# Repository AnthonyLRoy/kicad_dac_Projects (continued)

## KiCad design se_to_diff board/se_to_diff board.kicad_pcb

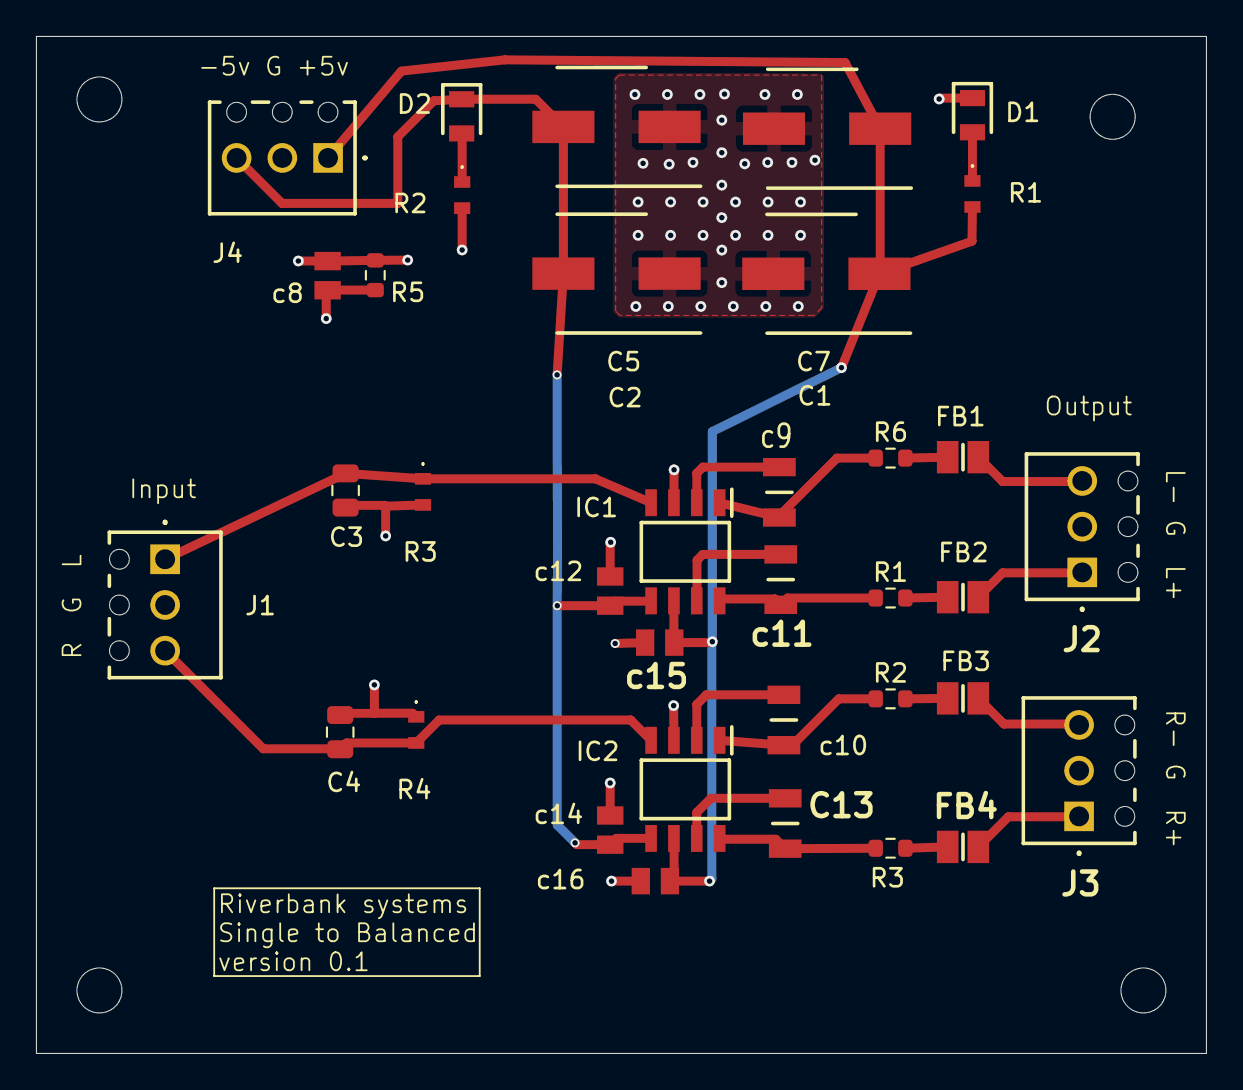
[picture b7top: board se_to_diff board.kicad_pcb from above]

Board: 4 copper layers, 65.0 x 56.5 mm, 40 parts (0 on the bottom side), 24 nets.

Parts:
C1, C2, C5, C7: 47u; CAPAE660X800N
C3, C4: 220p; C_0805_2012Metric
C13: 10u; CAPC3216X229N
D1, D2: LS_R976; LEDC2012X40N
FB1, FB2, FB3, FB4: NFZ2MSD101SZ10L; BEADC2016X120N
H1, H2, H3, H4: MountingHole; MountingHole_2.5mm
IC1, IC2: 1646S08-U; SOIC127P602X173-8N
J1, J2, J3, J4: 1725669
R1, R2#2, R3: 22; R_0603_1608Metric
R1#2, R2: 3k; ERJH3
R3#2, R4: 47k; ERJH3
R5: 10R; R_0603_1608Metric
R6: 22R; R_0603_1608Metric
c8, c12, c14, c15, c16: 100n; CAPC2012X94N
c9, c10, c11: 10u; CAPC3216X229N

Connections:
/Sout L +: FB2.1, R1.2
/Sout L -: FB1.1, R6.2
/Sout R +: FB4.1, R3.2
/Sout R -: FB3.1, R2#2.2
/in L: C3.2, IC1.4 (IN), J1.1, R3#2.1
/in R: C4.1, IC2.4 (IN), J1.3, R4.2
/out L +: IC1.8 (OUT+), R1.1, c11.2
/out L -: IC1.1 (OUT-), R6.1, c9.2
/out R +: C13.2, IC2.8 (OUT+), R3.1
/out R -: IC2.1 (OUT-), R2#2.1, c10.2
GND: C3.1, C4.2, IC1.3 (GND), IC2.3 (GND), J1.2, J2.2, J3.2, R3#2.2, R4.1, R5.2, c8.1
GND2: C1.2, C2.1, C5.1, C7.2, D1.1 (K), J4.2, R2.2, R5.1, c8.2, c12.1, c14.1, c15.1, c16.1
unnamed: D1.2 (A), R1#2.1
unnamed: D2.2 (A), R2.1
unnamed: FB1.2, J2.3
unnamed: FB2.2, J2.1
unnamed: FB3.2, J3.3
unnamed: FB4.2, J3.1
unnamed: IC1.7 (SNS+), c11.1
unnamed: IC1.2 (SNS-), c9.1
unnamed: C13.1, IC2.7 (SNS+)
unnamed: IC2.2 (SNS-), c10.1
VCC: C1.1, C7.1, IC1.6 (VCC), IC2.6 (VCC), J4.1, R1#2.2, c15.2, c16.2
VEE: C2.2, C5.2, D2.1 (K), IC1.5 (VEE), IC2.5 (VEE), J4.3, c12.2, c14.2

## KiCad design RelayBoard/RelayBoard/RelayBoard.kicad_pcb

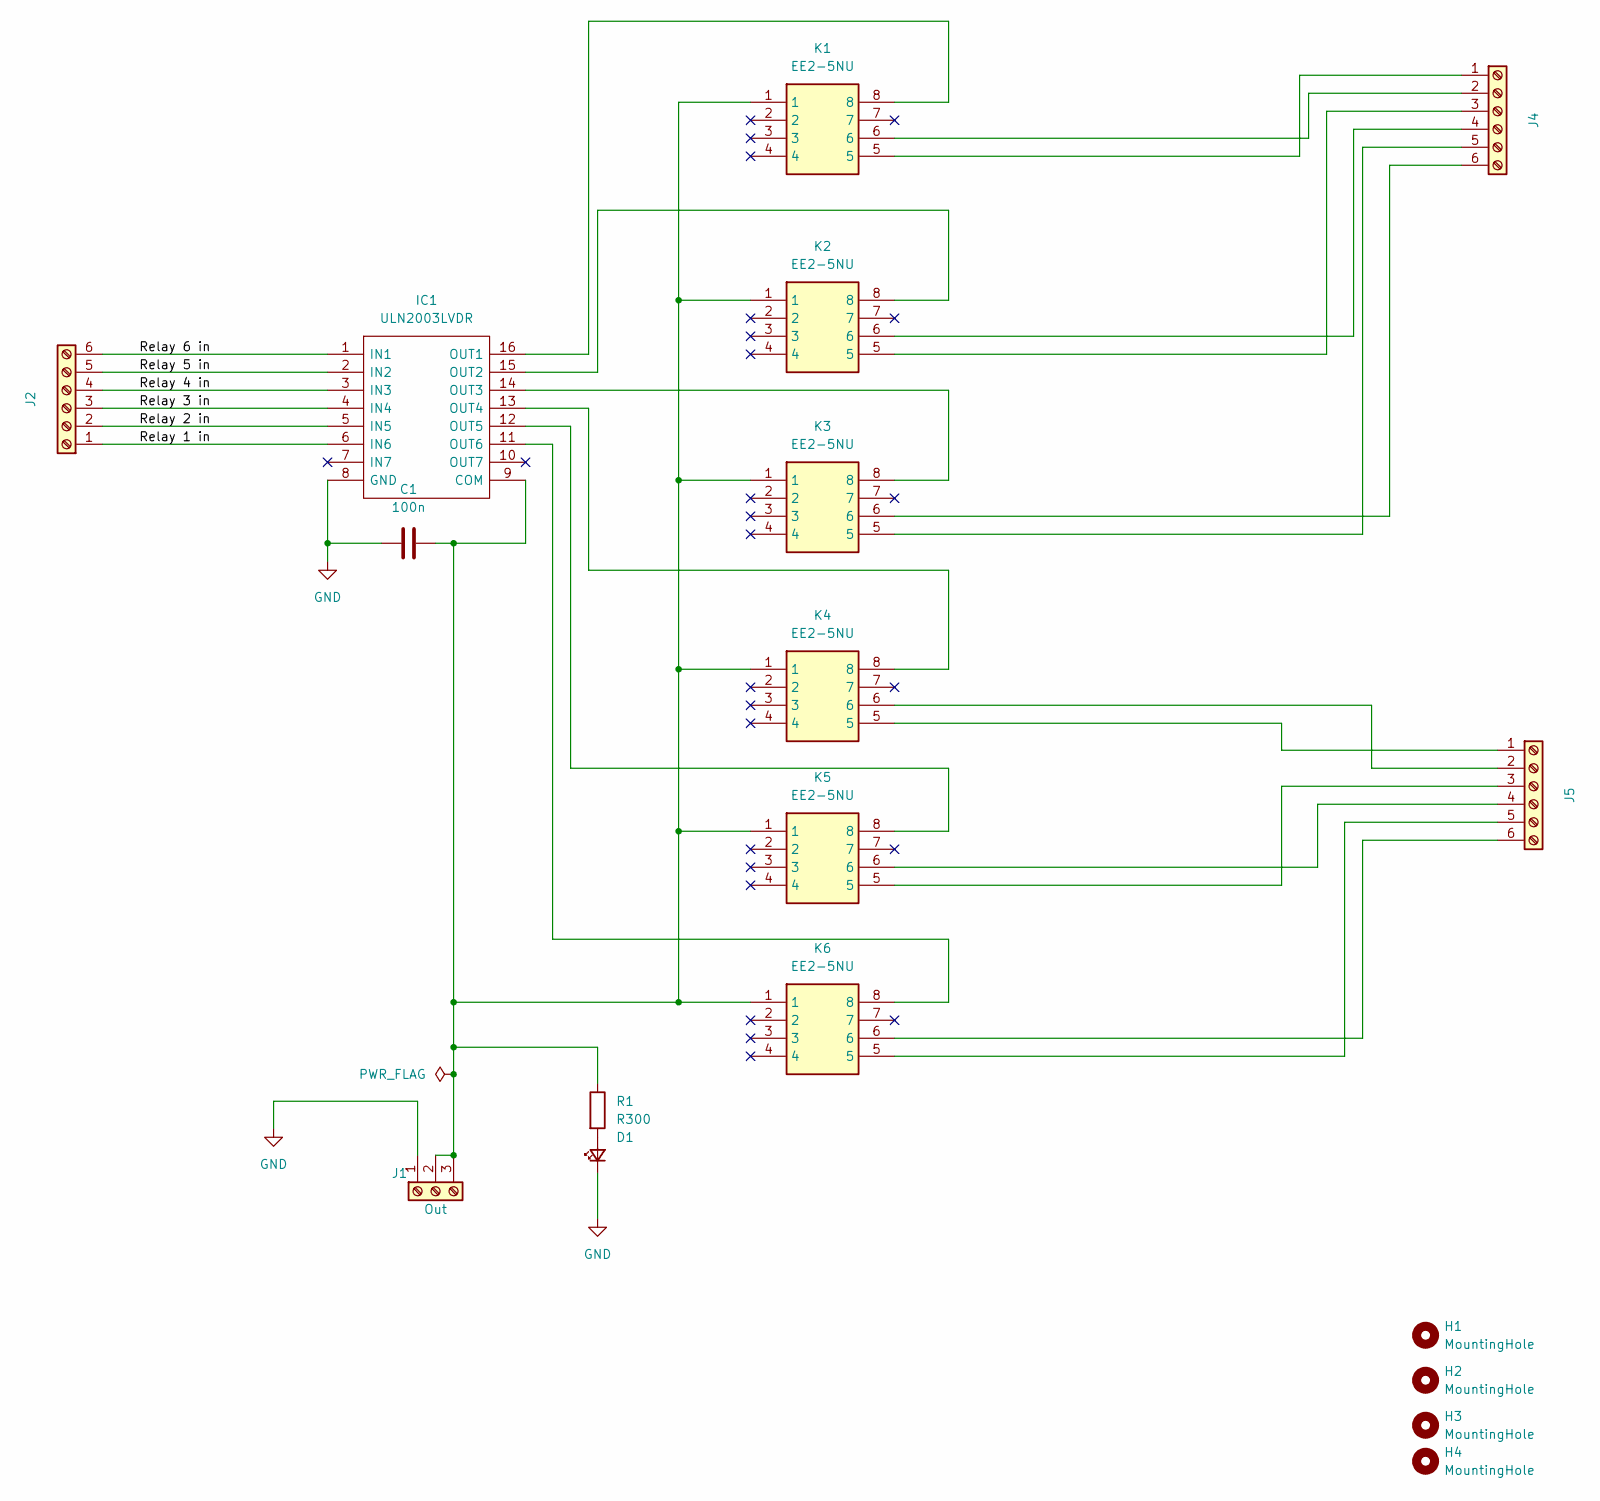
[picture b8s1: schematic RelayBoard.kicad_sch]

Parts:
C1: 100n; C_0805_2012Metric_Pad1.18x1.45mm_HandSolder
D1: LS_R976; LEDC2012X40N; Mouser Part Number 720-LSR976D5178
H1, H2, H3, H4: MountingHole; MountingHole_2.7mm_M2.5
IC1: ULN2003LVDR; SOIC127P780X200-16N; Manufacturer_Part_Number ULN2003LVDR; Mouser Part Number 595-ULN2003LVDR
J1: Out; PinHeader_1x03_P2.54mm_Vertical
J2, J4, J5: Buffer; PinHeader_1x06_P2.54mm_Vertical
K1, K2, K3, K4, K5, K6: EE2-5NU; Mouser Part Number 80-EE2-5NU
R1: R300; R_0603_1608Metric_Pad0.98x0.95mm_HandSolder

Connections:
/Relay 1 in: IC1.6 (IN6), J2.1
/Relay 2 in: IC1.5 (IN5), J2.2
/Relay 3 in: IC1.4 (IN4), J2.3
/Relay 4 in: IC1.3 (IN3), J2.4
/Relay 5 in: IC1.2 (IN2), J2.5
/Relay 6 in: IC1.1 (IN1), J2.6
GND: C1.1, D1.1 (K), IC1.8 (GND), J1.1
unnamed: D1.2 (A), R1.2
unnamed: C1.2, IC1.9 (COM), J1.2, J1.3, K1.1, K2.1, K3.1, K4.1, K5.1, K6.1, R1.1
unnamed: IC1.16 (OUT1), K1.8
unnamed: IC1.15 (OUT2), K2.8
unnamed: IC1.14 (OUT3), K3.8
unnamed: IC1.13 (OUT4), K4.8
unnamed: IC1.12 (OUT5), K5.8
unnamed: IC1.11 (OUT6), K6.8
unnamed: J4.1, K1.5
unnamed: J4.2, K1.6
unnamed: J4.3, K2.5
unnamed: J4.4, K2.6
unnamed: J4.5, K3.5
unnamed: J4.6, K3.6
unnamed: J5.1, K4.5
unnamed: J5.2, K4.6
unnamed: J5.3, K5.5
unnamed: J5.4, K5.6
unnamed: J5.5, K6.5
unnamed: J5.6, K6.6

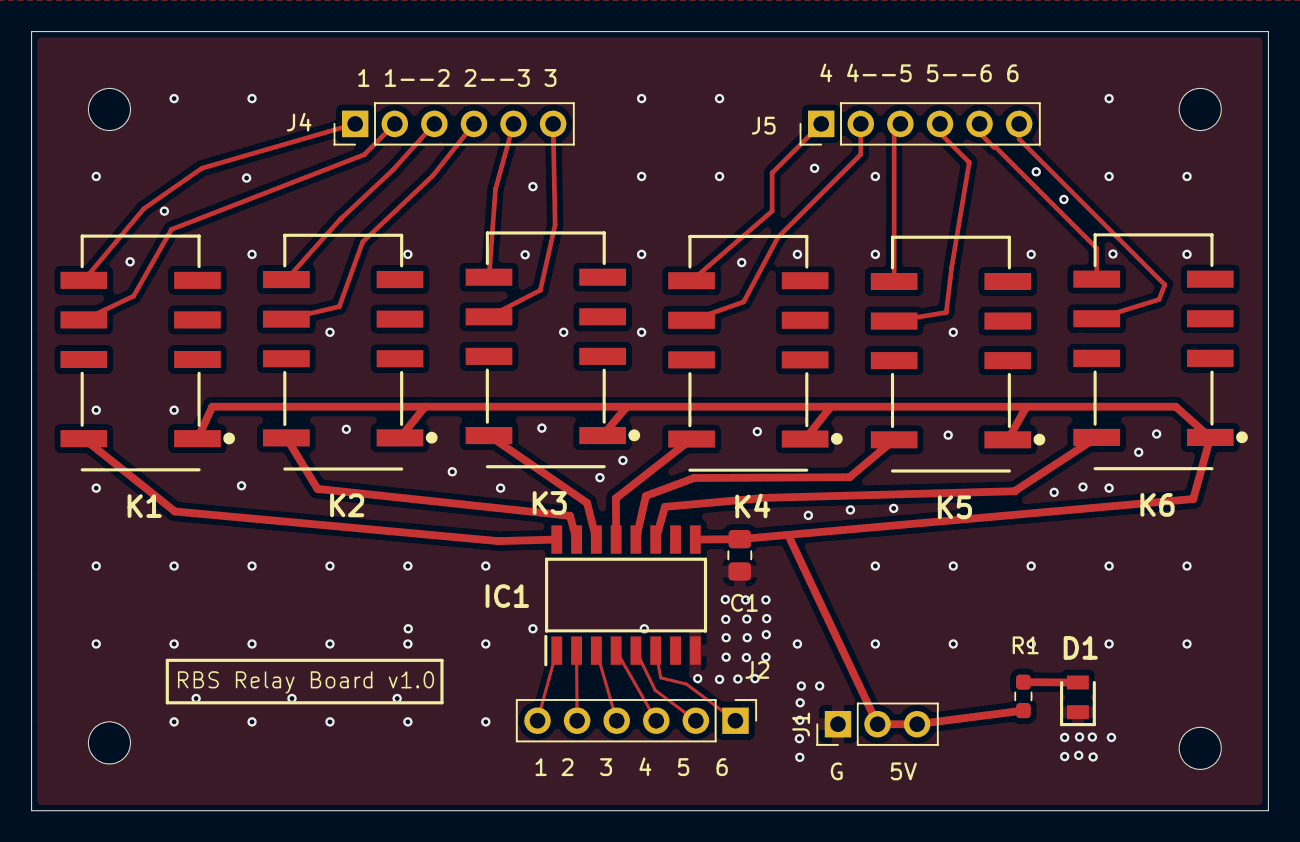
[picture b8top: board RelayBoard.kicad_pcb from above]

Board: 2 copper layers, 79.4 x 50.0 mm, 18 parts (0 on the bottom side), 27 nets.
